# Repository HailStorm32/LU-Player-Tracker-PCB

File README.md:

# Description
This repository holds the Eagle CAD PCB files for the LU Player Tracker board. You can find the code repository [here](https://github.com/HailStorm32/LU-Player-Tracker-Code). 

This board shows the player count and locations in real time by lighting up the respective world RGB LED and seven segment display. The player location and count is sent via MQTT from a Darkflame Universe private server. 

> Darkflame Universe is a server emulator for the defunct LEGO Universe MMO. You can find more info about the project [here](https://github.com/DarkflameUniverse/DarkflameServer)

# BOM

*Spreadsheet also in the repo*

---

Credit to `FutronBob` for the map layout that inspired this project

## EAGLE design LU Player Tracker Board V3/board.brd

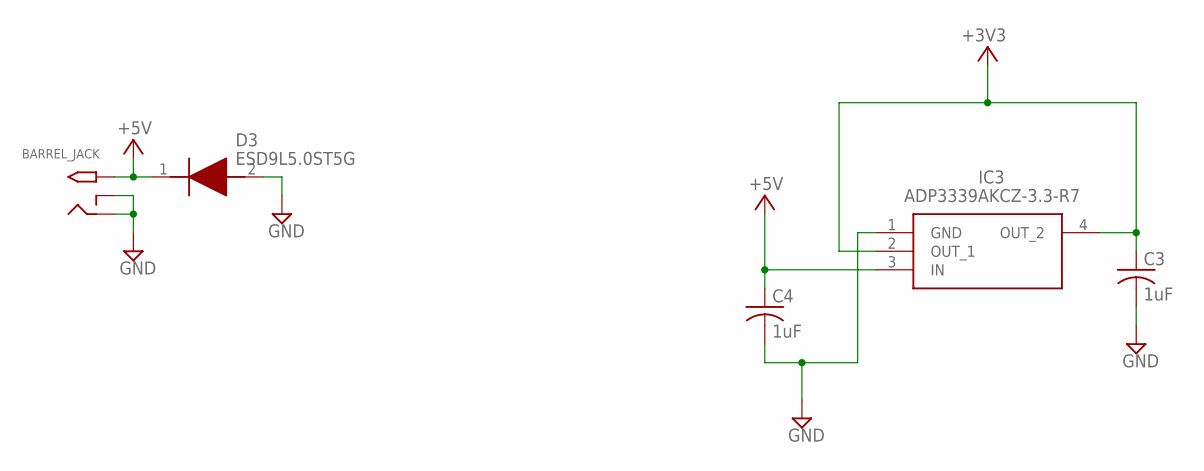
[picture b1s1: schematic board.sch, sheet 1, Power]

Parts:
BARREL_JACK: 2.1MMJACKTHM; PJ-102A
C3, C4: 1uF; C0402
D3: ESD9L5.0ST5G; SODFL1006X40N
IC3: ADP3339AKCZ-3.3-R7; SOT230P700X180-4N

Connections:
+3V3: C3.1, IC3.2 (OUT_1), IC3.4 (OUT_2); also elsewhere on the board
+5V: BARREL_JACK.TIP, C4.1, D3.1 (K), IC3.3 (IN); also elsewhere on the board
GND: BARREL_JACK.RING, BARREL_JACK.RING_SW, C3.2, C4.2, D3.2 (A), IC3.1 (GND); also elsewhere on the board

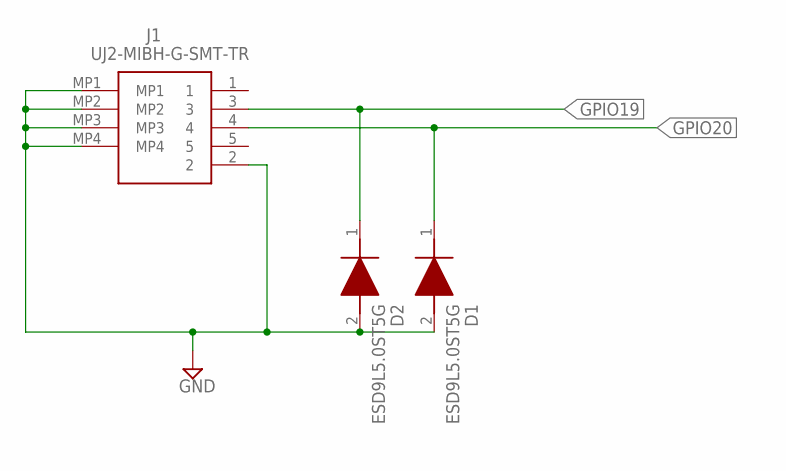
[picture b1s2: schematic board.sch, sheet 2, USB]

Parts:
D1, D2: ESD9L5.0ST5G; SODFL1006X40N
J1: UJ2-MIBH-G-SMT-TR; UJ2MIBHGSMTTR

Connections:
GND: D1.2 (A), D2.2 (A), J1.2, J1.MP1, J1.MP2, J1.MP3, J1.MP4; also elsewhere on the board
GPIO19: D2.1 (K), J1.3; also elsewhere on the board
GPIO20: D1.1 (K), J1.4; also elsewhere on the board

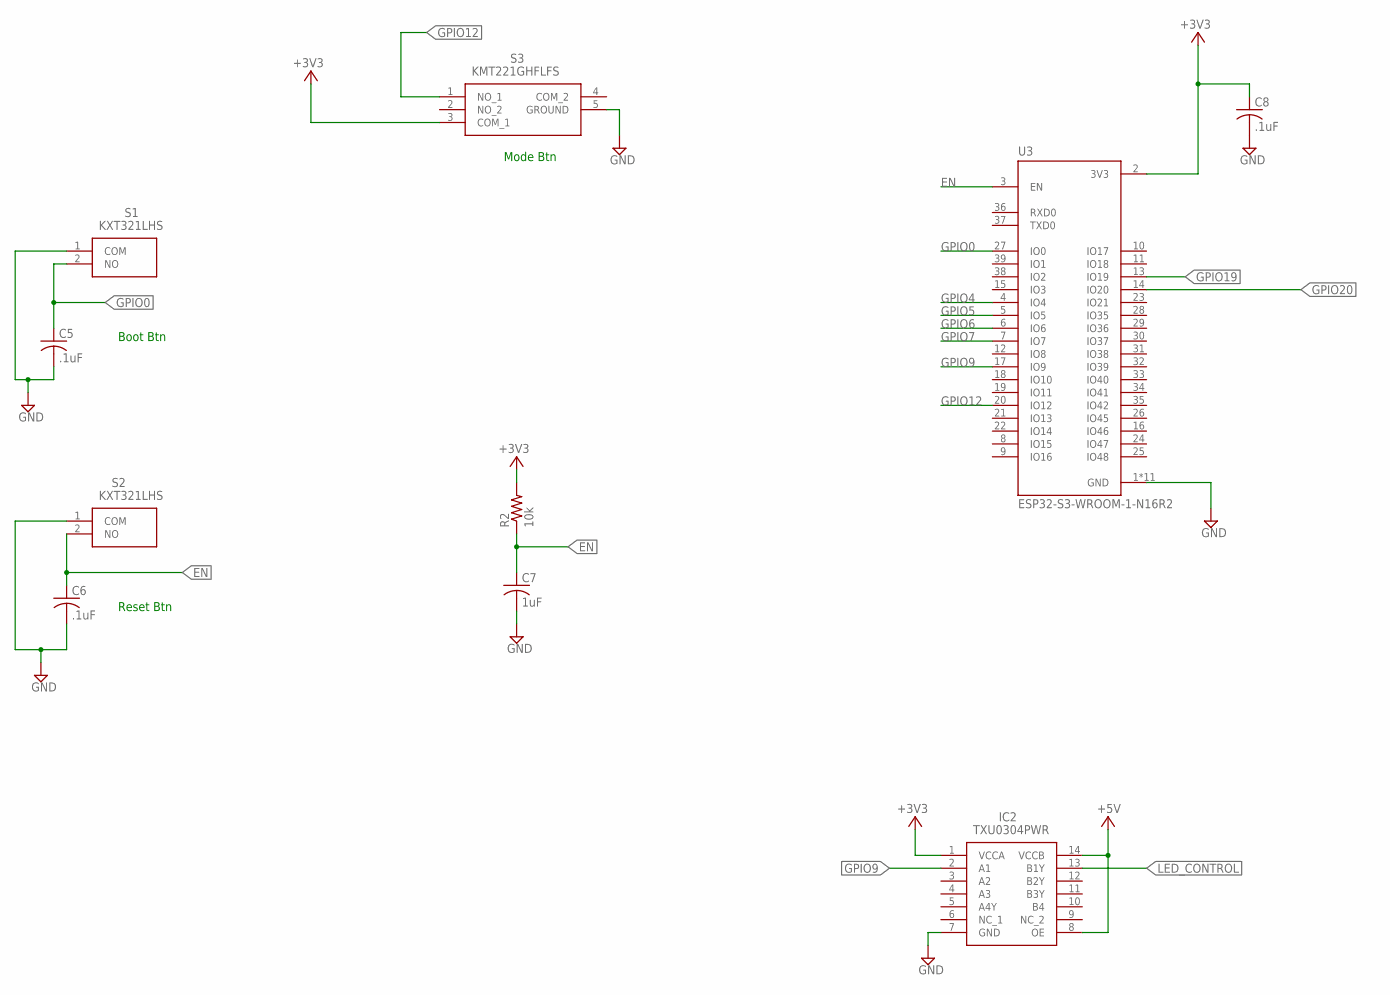
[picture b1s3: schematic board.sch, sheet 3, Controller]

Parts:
C5, C6, C8: .1uF; C0402
C7: 1uF; C0402
IC2: TXU0304PWR; SOP65P640X120-14N
R2: 10k; R0402
S1, S2: KXT321LHS
S3: KMT221GHFLFS
U3: ESP32-S3-WROOM-1-N16R2; XCVR_ESP32-S3-WROOM-1-N16R2

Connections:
+3V3: C8.1, IC2.1 (VCCA), R2.2, S3.3 (COM_1), U3.2 (3V3); also elsewhere on the board
+5V: IC2.8 (OE), IC2.14 (VCCB); also elsewhere on the board
EN: C6.1, C7.1, R2.1, S2.2 (NO), U3.3 (EN)
GND: C5.2, C6.2, C7.2, C8.2, IC2.7 (GND), S1.1 (COM), S2.1 (COM), S3.5 (GROUND), U3.1 (GND), U3.40 (GND), U3.41_1 (GND), U3.41_2 (GND), U3.41_3 (GND), U3.41_4 (GND), U3.41_5 (GND), U3.41_6 (GND), U3.41_7 (GND), U3.41_8 (GND), U3.41_9 (GND); also elsewhere on the board
GPIO0: C5.1, S1.2 (NO), U3.27 (IO0)
GPIO4: U3.4 (IO4); also elsewhere on the board
GPIO5: U3.5 (IO5); also elsewhere on the board
GPIO6: U3.6 (IO6); also elsewhere on the board
GPIO7: U3.7 (IO7); also elsewhere on the board
GPIO9: IC2.2 (A1), U3.17 (IO9)
GPIO12: S3.1 (NO_1), U3.20 (IO12)
GPIO19: U3.13 (IO19); also elsewhere on the board
GPIO20: U3.14 (IO20); also elsewhere on the board
LED_CONTROL: IC2.13 (B1Y); also elsewhere on the board

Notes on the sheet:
Reset Btn
Boot Btn
Mode Btn

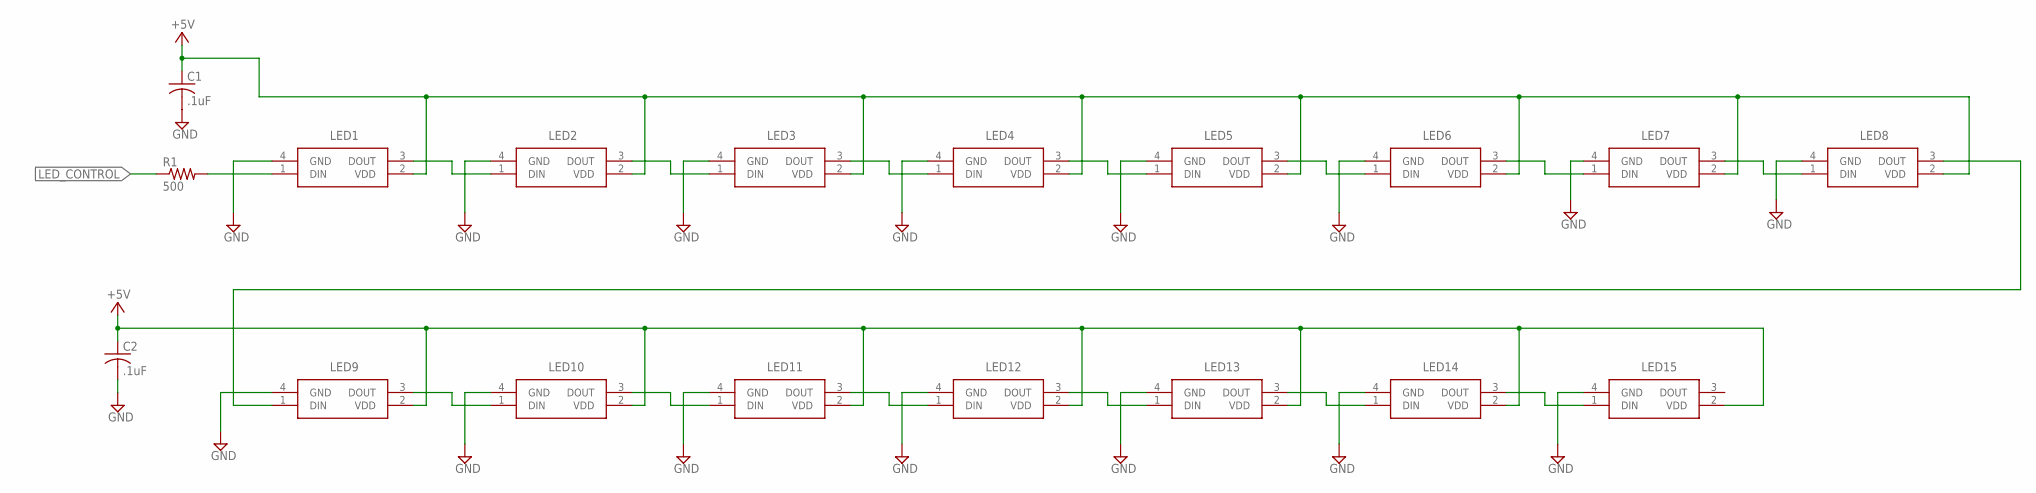
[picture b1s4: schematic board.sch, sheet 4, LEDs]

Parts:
C1, C2: .1uF; C0402
LED1, LED2, LED3, LED4, LED5, LED6, LED7, LED8, LED9, LED10, LED11, LED12, LED13, LED14, LED15: 4492__SK6805-EC_15_; 4492SK6805EC15
R1: 500; R0402

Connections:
+5V: C1.1, C2.1, LED1.2 (VDD), LED2.2 (VDD), LED3.2 (VDD), LED4.2 (VDD), LED5.2 (VDD), LED6.2 (VDD), LED7.2 (VDD), LED8.2 (VDD), LED9.2 (VDD), LED10.2 (VDD), LED11.2 (VDD), LED12.2 (VDD), LED13.2 (VDD), LED14.2 (VDD), LED15.2 (VDD); also elsewhere on the board
GND: C1.2, C2.2, LED1.4 (GND), LED2.4 (GND), LED3.4 (GND), LED4.4 (GND), LED5.4 (GND), LED6.4 (GND), LED7.4 (GND), LED8.4 (GND), LED9.4 (GND), LED10.4 (GND), LED11.4 (GND), LED12.4 (GND), LED13.4 (GND), LED14.4 (GND), LED15.4 (GND); also elsewhere on the board
LED_CONTROL: R1.1; also elsewhere on the board
unnamed: LED1.3 (DOUT), LED2.1 (DIN)
unnamed: LED2.3 (DOUT), LED3.1 (DIN)
unnamed: LED3.3 (DOUT), LED4.1 (DIN)
unnamed: LED4.3 (DOUT), LED5.1 (DIN)
unnamed: LED5.3 (DOUT), LED6.1 (DIN)
unnamed: LED6.3 (DOUT), LED7.1 (DIN)
unnamed: LED7.3 (DOUT), LED8.1 (DIN)
unnamed: LED8.3 (DOUT), LED9.1 (DIN)
unnamed: LED9.3 (DOUT), LED10.1 (DIN)
unnamed: LED10.3 (DOUT), LED11.1 (DIN)
unnamed: LED11.3 (DOUT), LED12.1 (DIN)
unnamed: LED12.3 (DOUT), LED13.1 (DIN)
unnamed: LED13.3 (DOUT), LED14.1 (DIN)
unnamed: LED14.3 (DOUT), LED15.1 (DIN)
unnamed: LED1.1 (DIN), R1.2

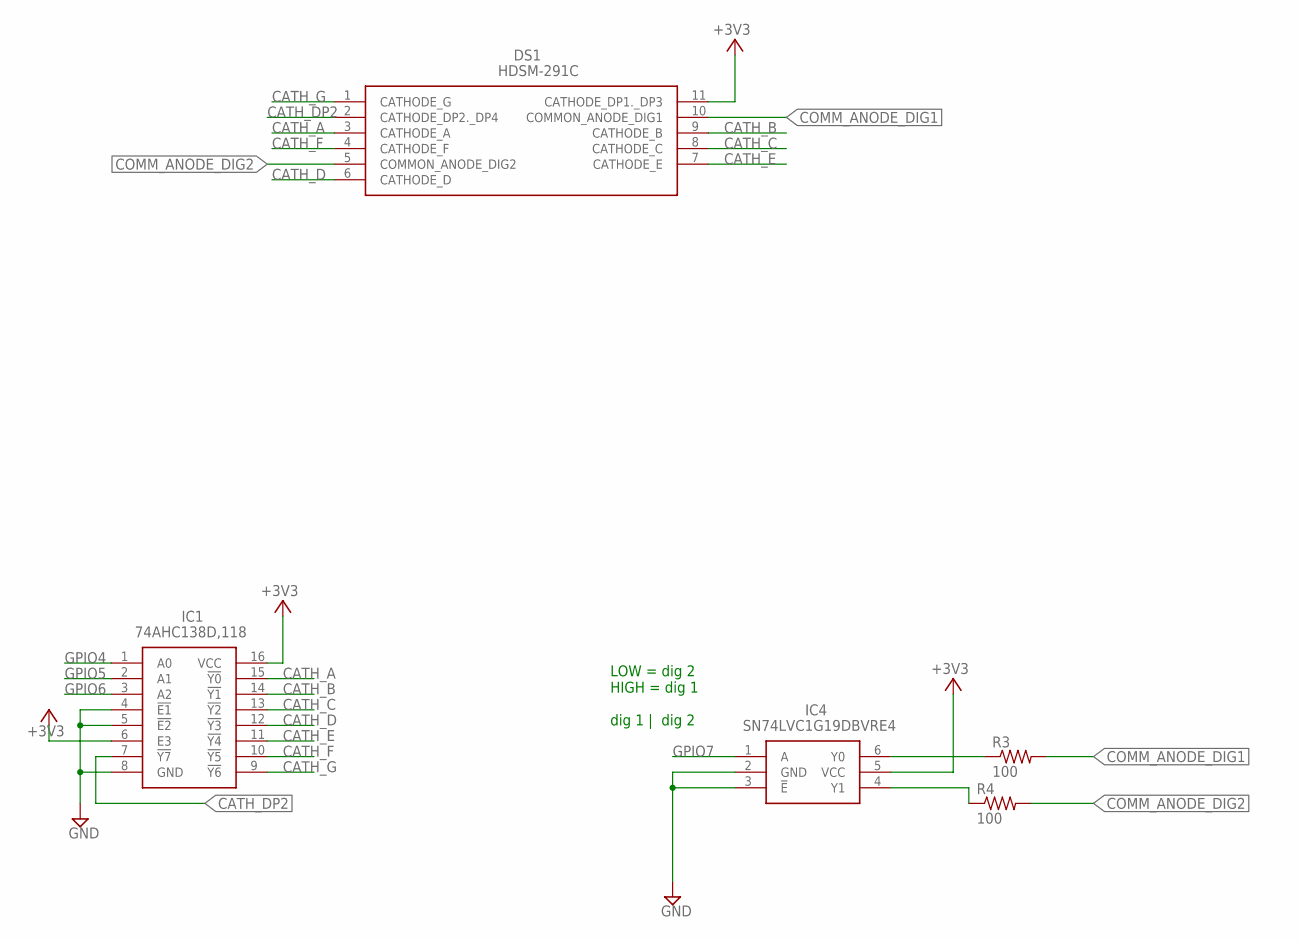
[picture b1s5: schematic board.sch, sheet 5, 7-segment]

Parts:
DS1: HDSM-291C; HDSM291C
IC1: 74AHC138D,118; SOIC127P600X175-16N
IC4: SN74LVC1G19DBVRE4; SOT95P280X145-6N
R3, R4: 100; R0402

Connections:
+3V3: DS1.11 (CATHODE_DP1._DP3), IC1.6 (E3), IC1.16 (VCC), IC4.5 (VCC); also elsewhere on the board
CATH_A: DS1.3 (CATHODE_A), IC1.15 (!Y0)
CATH_B: DS1.9 (CATHODE_B), IC1.14 (!Y1)
CATH_C: DS1.8 (CATHODE_C), IC1.13 (!Y2)
CATH_D: DS1.6 (CATHODE_D), IC1.12 (!Y3)
CATH_DP2: DS1.2 (CATHODE_DP2._DP4), IC1.7 (!Y7)
CATH_E: DS1.7 (CATHODE_E), IC1.11 (!Y4)
CATH_F: DS1.4 (CATHODE_F), IC1.10 (!Y5)
CATH_G: DS1.1 (CATHODE_G), IC1.9 (!Y6)
COMM_ANODE_DIG1: DS1.10 (COMMON_ANODE_DIG1), R3.2
COMM_ANODE_DIG2: DS1.5 (COMMON_ANODE_DIG2), R4.2
GND: IC1.4 (!E1), IC1.5 (!E2), IC1.8 (GND), IC4.2 (GND), IC4.3 (!E); also elsewhere on the board
GPIO4: IC1.1 (A0); also elsewhere on the board
GPIO5: IC1.2 (A1); also elsewhere on the board
GPIO6: IC1.3 (A2); also elsewhere on the board
GPIO7: IC4.1 (A); also elsewhere on the board
unnamed: IC4.6 (Y0), R3.1
unnamed: IC4.4 (Y1), R4.1

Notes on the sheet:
LOW = dig 2 HIGH = dig 1 dig 1 | dig 2

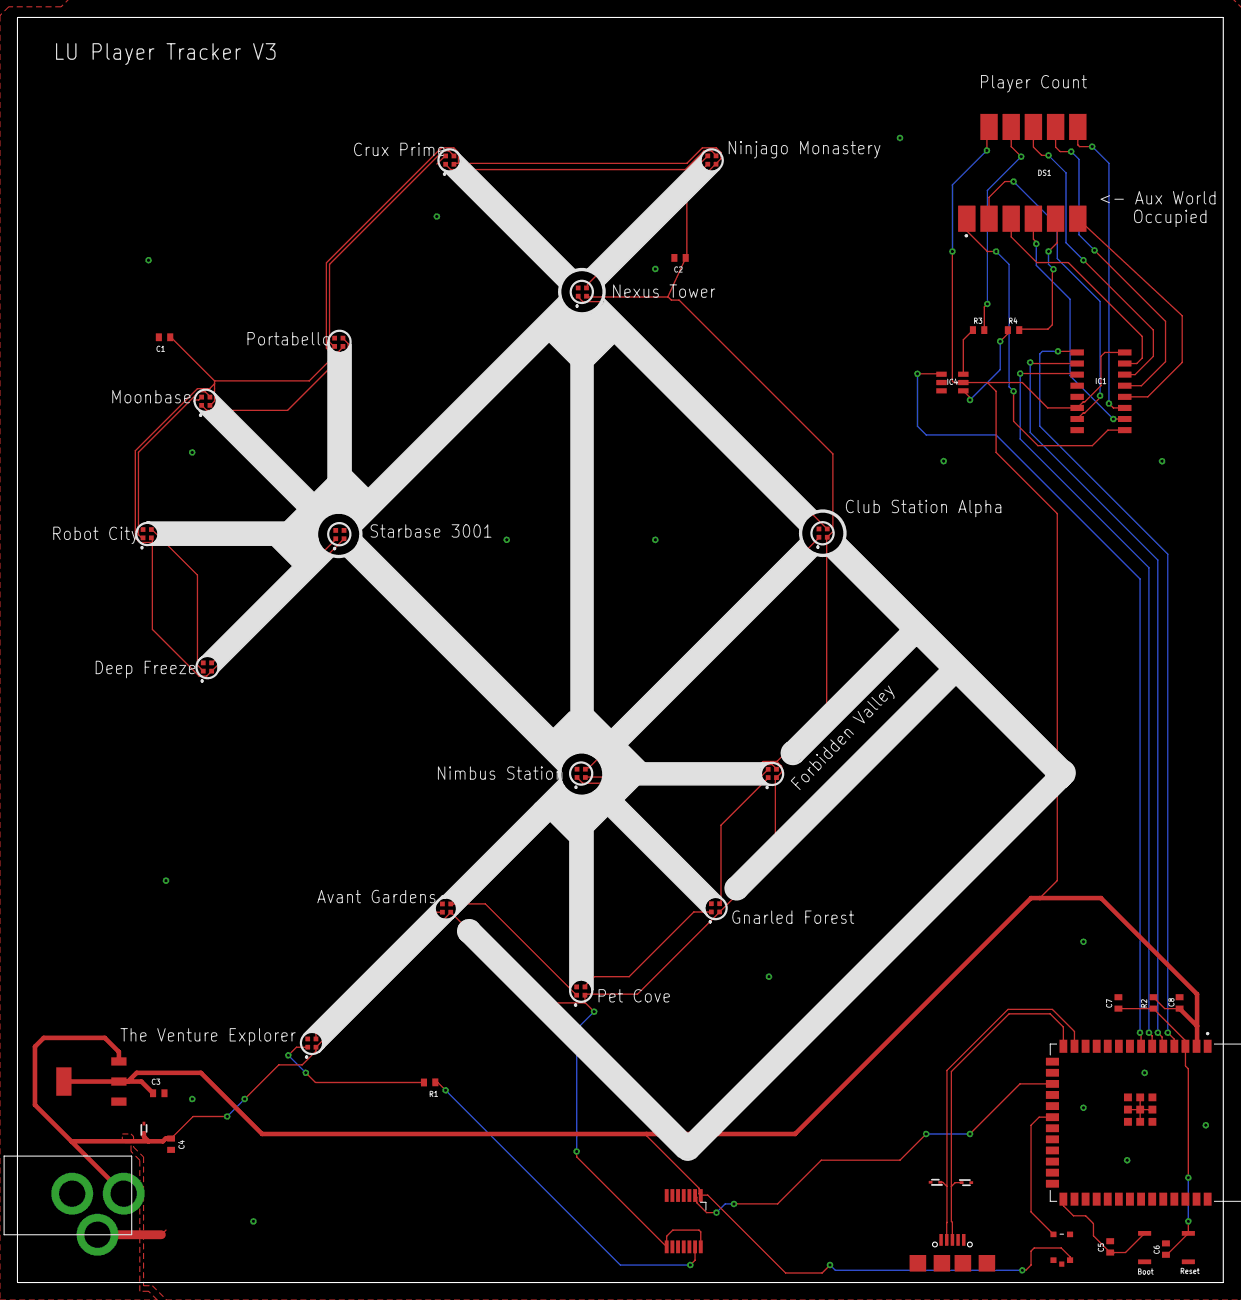
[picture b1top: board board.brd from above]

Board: 2 copper layers, 138.0 x 144.8 mm, 41 parts (0 on the bottom side), 41 nets.

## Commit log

2022-12-07 added files
2022-12-07 Added all the main lines
2022-12-17 Updated to V2
2023-01-22 v3 of board
2023-02-11 resistor change
2023-02-19 updated gitignore
2023-02-26 Added BOM
2023-02-26 Added README
